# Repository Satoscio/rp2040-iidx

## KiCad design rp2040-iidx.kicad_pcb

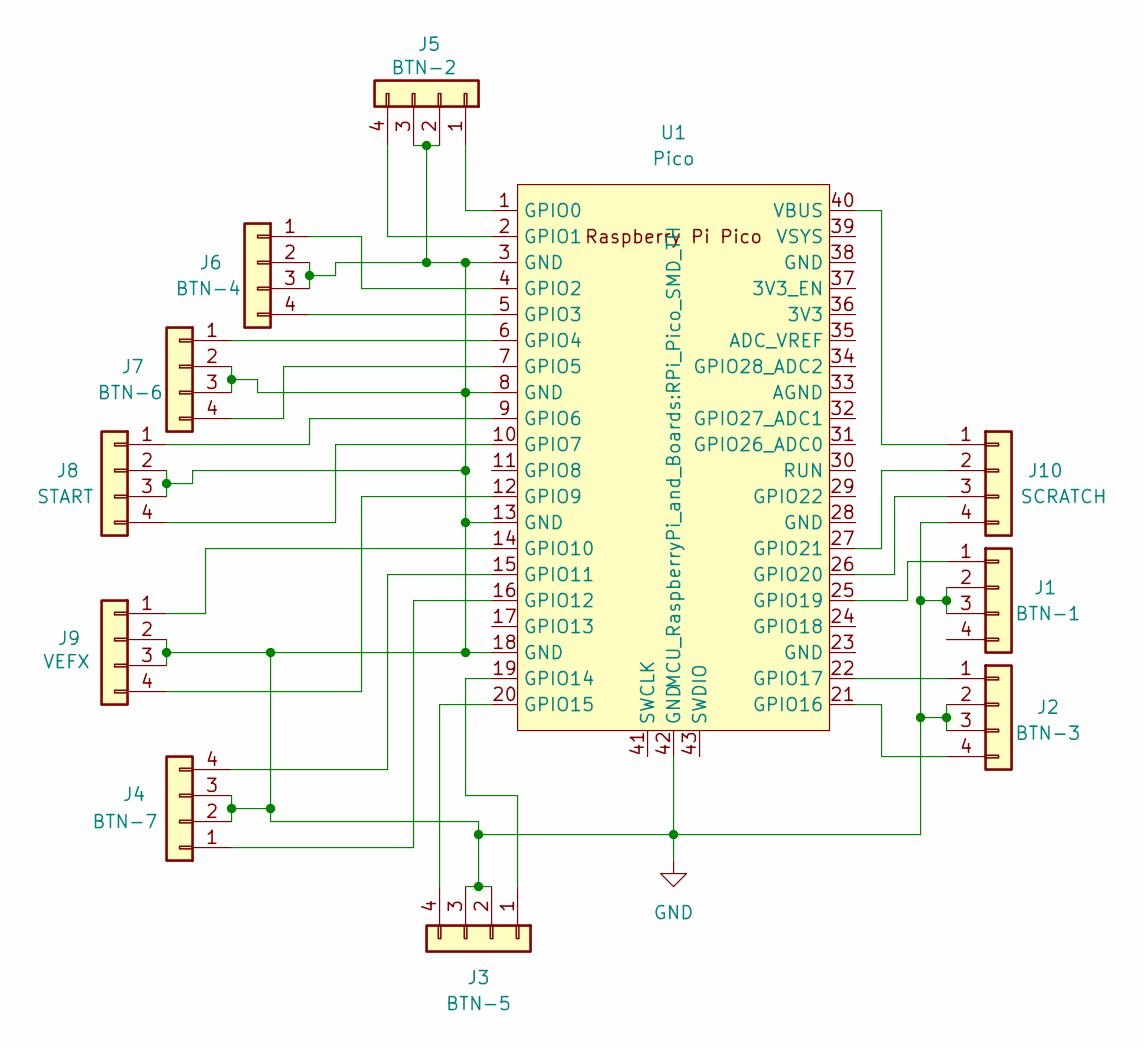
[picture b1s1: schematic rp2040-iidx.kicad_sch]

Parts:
J1: BTN-1; PinHeader_1x04_P2.54mm_Vertical
J2: BTN-3; PinHeader_1x04_P2.54mm_Vertical
J3: BTN-5; PinHeader_1x04_P2.54mm_Vertical
J4: BTN-7; PinHeader_1x04_P2.54mm_Vertical
J5: BTN-2; PinHeader_1x04_P2.54mm_Vertical
J6: BTN-4; PinHeader_1x04_P2.54mm_Vertical
J7: BTN-6; PinHeader_1x04_P2.54mm_Vertical
J8: START; PinHeader_1x04_P2.54mm_Vertical
J9: VEFX; PinHeader_1x04_P2.54mm_Vertical
J10: SCRATCH; PinHeader_1x04_P2.54mm_Vertical
U1: Pico; RPi_Pico_SMD_TH

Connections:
GND: J1.2, J1.3, J2.2, J2.3, J3.2, J3.3, J4.2, J4.3, J5.2, J5.3, J6.2, J6.3, J7.2, J7.3, J8.2, J8.3, J9.2, J9.3, J10.4, U1.3 (GND), U1.8 (GND), U1.13 (GND), U1.18 (GND), U1.42 (GND)
unnamed: J1.1, U1.25 (GPIO19)
unnamed: J2.1, U1.22 (GPIO17)
unnamed: J2.4, U1.21 (GPIO16)
unnamed: J3.1, U1.19 (GPIO14)
unnamed: J3.4, U1.20 (GPIO15)
unnamed: J4.1, U1.16 (GPIO12)
unnamed: J4.4, U1.15 (GPIO11)
unnamed: J5.1, U1.1 (GPIO0)
unnamed: J5.4, U1.2 (GPIO1)
unnamed: J6.1, U1.4 (GPIO2)
unnamed: J6.4, U1.5 (GPIO3)
unnamed: J7.1, U1.6 (GPIO4)
unnamed: J7.4, U1.7 (GPIO5)
unnamed: J8.1, U1.9 (GPIO6)
unnamed: J8.4, U1.10 (GPIO7)
unnamed: J9.1, U1.14 (GPIO10)
unnamed: J9.4, U1.12 (GPIO9)
unnamed: J10.1, U1.40 (VBUS)
unnamed: J10.2, U1.27 (GPIO21)
unnamed: J10.3, U1.26 (GPIO20)

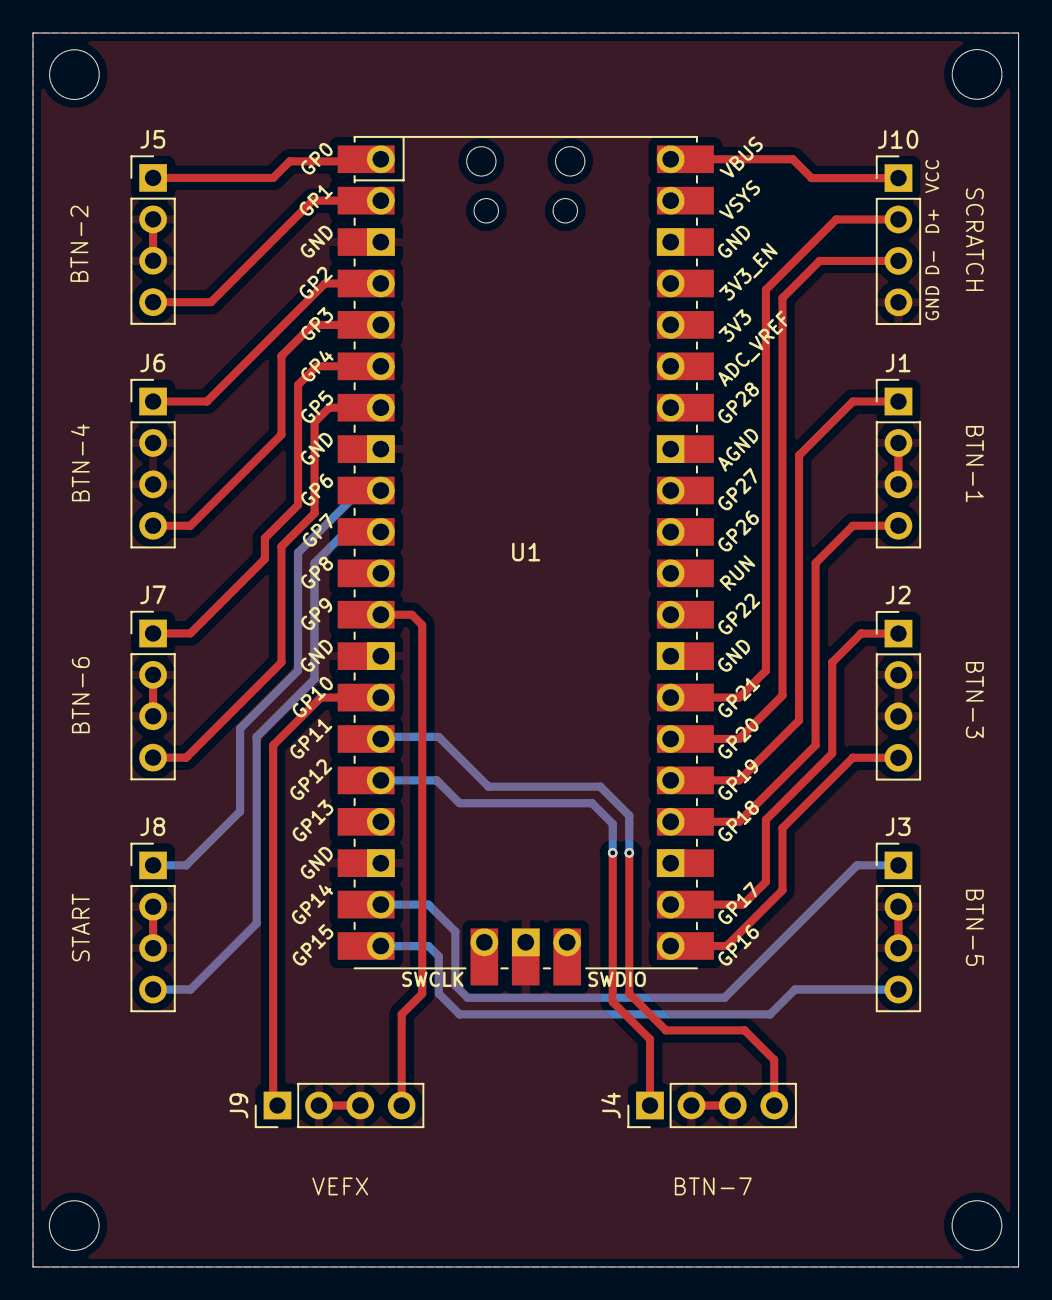
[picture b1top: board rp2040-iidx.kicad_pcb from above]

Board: 2 copper layers, 60.5 x 75.7 mm, 11 parts (0 on the bottom side), 21 nets.

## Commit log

2025-01-09 primo
